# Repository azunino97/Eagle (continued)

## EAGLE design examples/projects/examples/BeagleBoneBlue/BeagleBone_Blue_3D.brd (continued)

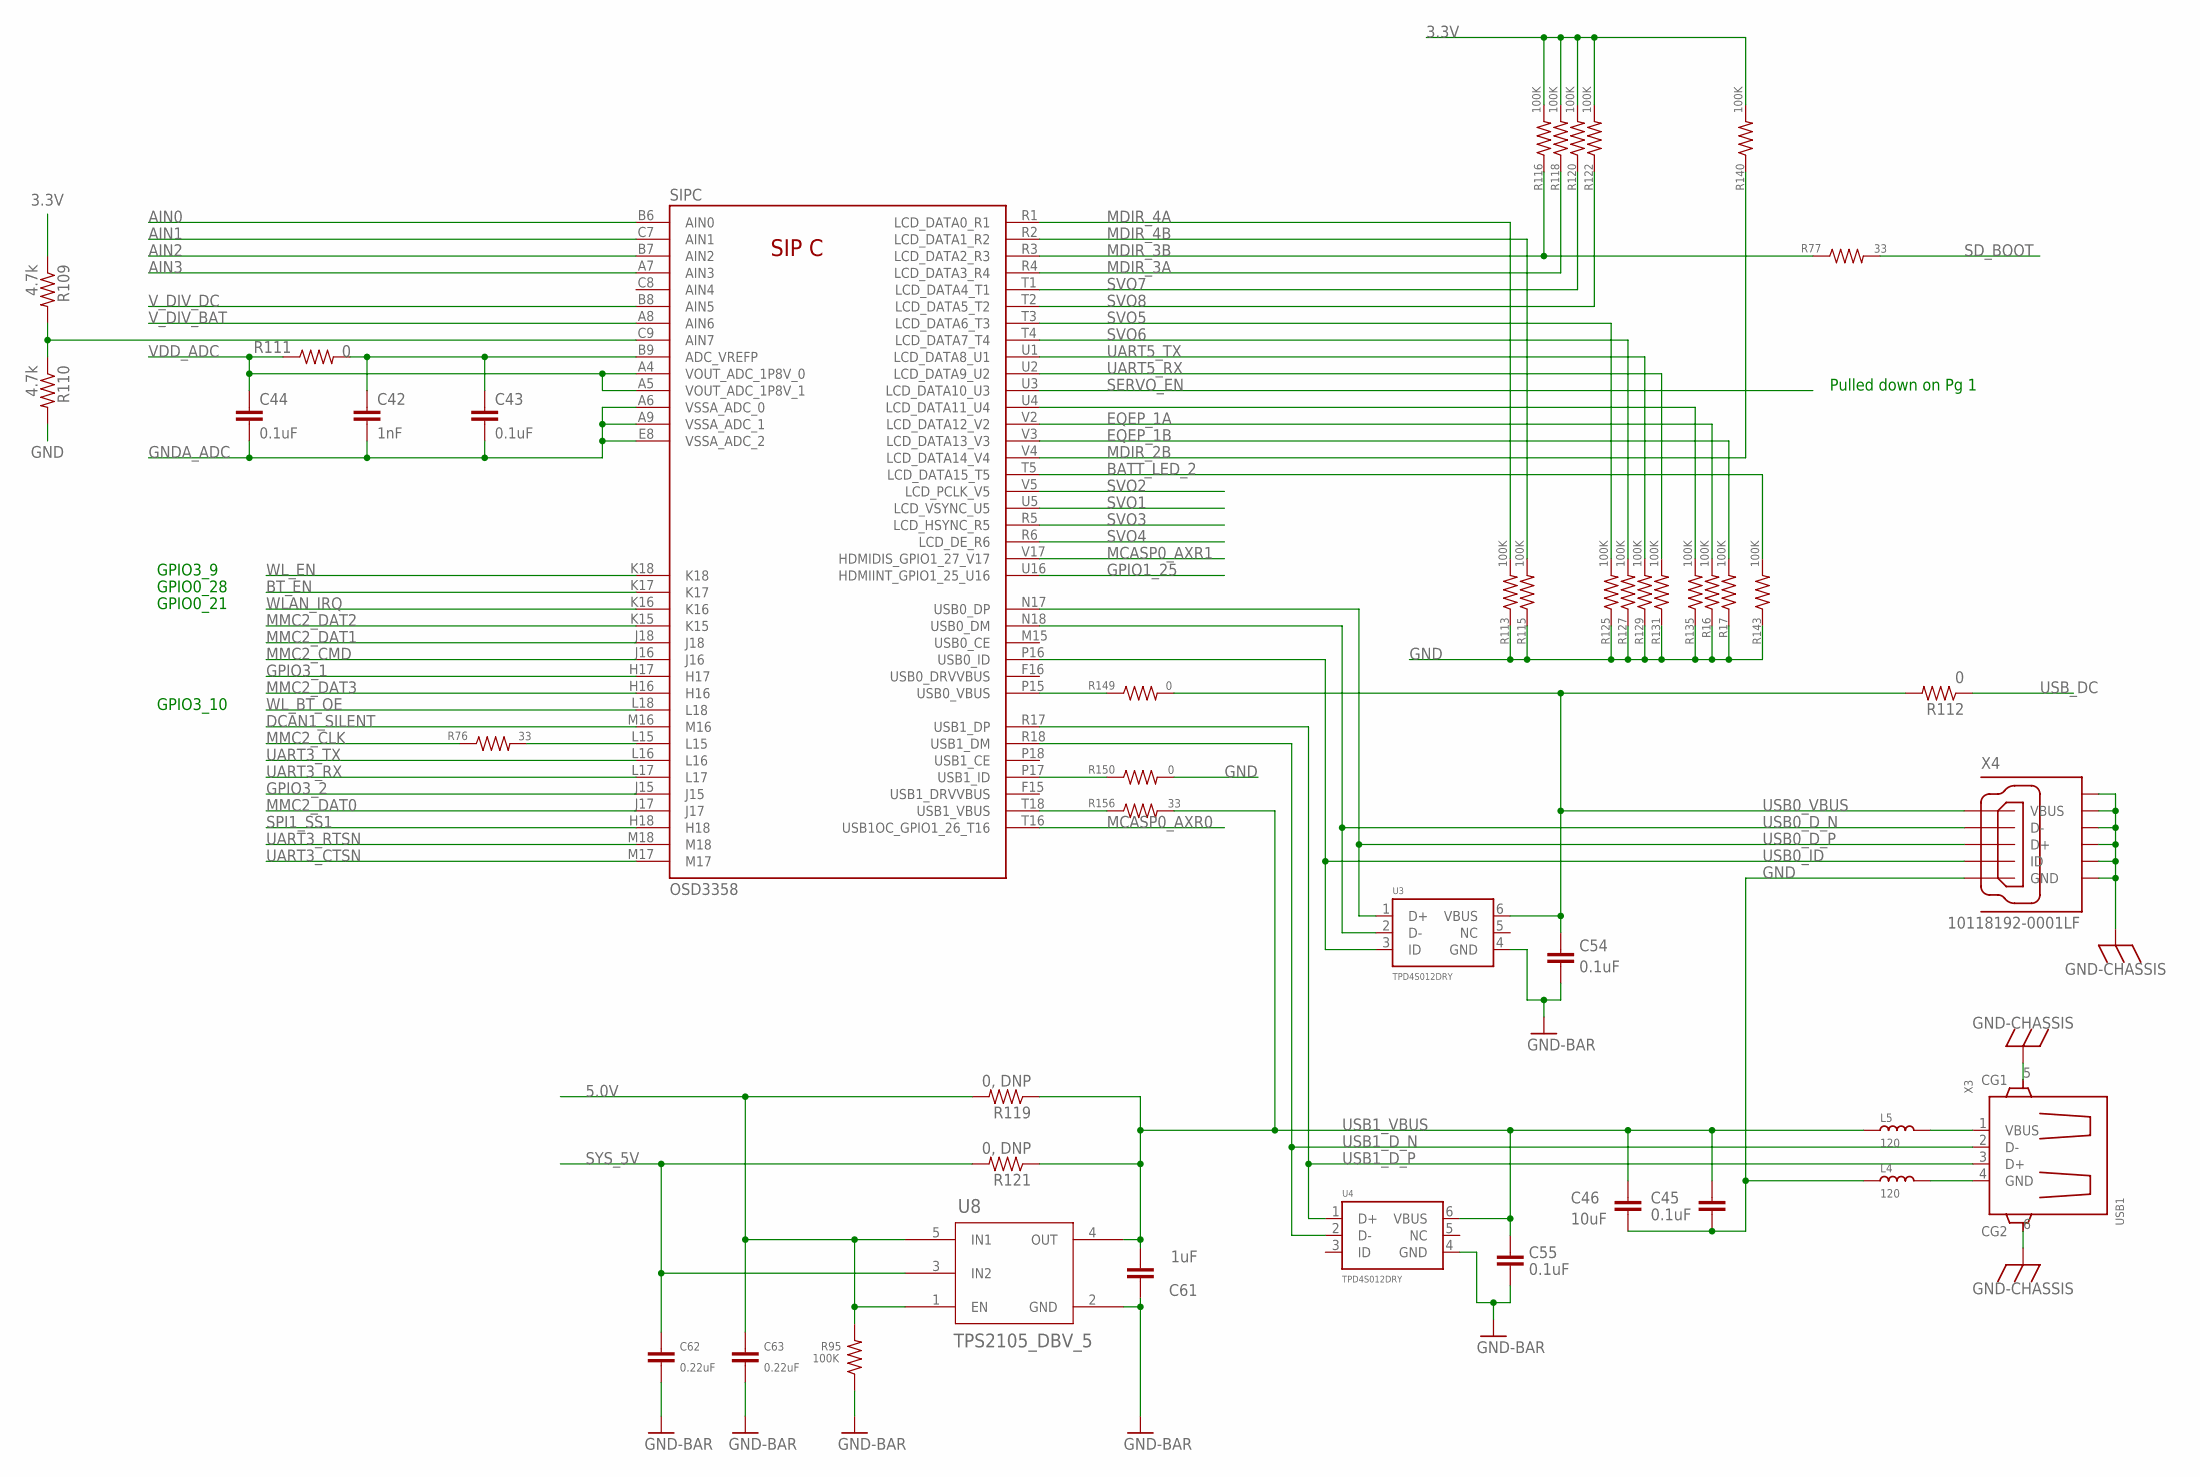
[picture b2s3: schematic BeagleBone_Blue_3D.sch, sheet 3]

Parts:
C42: 1nF; 0402-CAP
C43, C44, C45, C54, C55: 0.1uF; 0402-CAP
C46: 10uF; 0805
C61: 1uF; 0402-CAP
C62, C63: 0.22uF; 0402-CAP
L4, L5: 120; INDUCTOR_L0603
R16, R17, R95, R113, R115, R116, R118, R120, R122, R125, R127, R129, R131, R135, R140, R143: 100K; 0402-RES
R76, R77, R156: 33; 0402-RES
R109, R110: 4.7k; 0402-RES
R111, R149, R150: 0; 0402-RES
R112: 0; R0603
R119, R121: 0, DNP; R0603
SIP: OSD3358
U3, U4: TPD4S012DRY; SON-6(TI)-DRY
U8: TPS2105_DBV_5; DIODE_DBV5
X3: USB1; GHI2_USB_HOST_HORIZONTAL_W/CHASSIS_GND
X4: 10118192-0001LF; GHI-CONNECTORS_10118192-0001LF(MICRO-USB-B-AMPHENOL-FCI)

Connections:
3.3V: R109.1, R116.2, R118.2, R120.2, R122.2, R140.2; also elsewhere on the board
5.0V: C63.1, R95.2, R119.2, U8.1 (EN), U8.5 (IN1); also elsewhere on the board
AIN0: SIP.B6 (AIN0); also elsewhere on the board
AIN1: SIP.C7 (AIN1); also elsewhere on the board
AIN2: SIP.B7 (AIN2); also elsewhere on the board
AIN3: SIP.A7 (AIN3); also elsewhere on the board
BATT_LED_2: R143.2, SIP.T5 (LCD_DATA15_T5); also elsewhere on the board
BT_EN: SIP.K17; also elsewhere on the board
CGND: X3.5 (CG1), X3.6 (CG2), X4.CGND1 (SGND1), X4.CGND2 (SGND2), X4.CGND3 (SGND3), X4.CGND4 (SGND4), X4.CGND5 (SGND5), X4.CGND6 (SGND6); also elsewhere on the board
DCAN1_SILENT: SIP.M16; also elsewhere on the board
EQEP_1A: R16.2, SIP.V2 (LCD_DATA12_V2); also elsewhere on the board
EQEP_1B: R17.2, SIP.V3 (LCD_DATA13_V3); also elsewhere on the board
GND: C45.2, C46.2, C54.2, C55.2, C61.1, C62.2, C63.2, L4.1, R16.1, R17.1, R95.1, R110.2, R113.1, R115.1, R125.1, R127.1, R129.1, R131.1, R135.1, R143.1, R150.2, U3.4 (GND), U4.4 (GND), U8.2 (GND), X4.GND; also elsewhere on the board
GNDA_ADC: C42.2, C43.2, C44.2, SIP.A6 (VSSA_ADC_0), SIP.A9 (VSSA_ADC_1), SIP.E8 (VSSA_ADC_2)
GPIO1_25: SIP.U16 (HDMIINT_GPIO1_25_U16); also elsewhere on the board
GPIO3_1: SIP.H17; also elsewhere on the board
GPIO3_2: SIP.J15; also elsewhere on the board
MCASP0_AXR0: SIP.T16 (USB1OC_GPIO1_26_T16); also elsewhere on the board
MCASP0_AXR1: SIP.V17 (HDMIDIS_GPIO1_27_V17); also elsewhere on the board
MDIR_2B: R140.1, SIP.V4 (LCD_DATA14_V4); also elsewhere on the board
MDIR_3A: R118.1, SIP.R4 (LCD_DATA3_R4); also elsewhere on the board
MDIR_3B: R77.1, R116.1, SIP.R3 (LCD_DATA2_R3); also elsewhere on the board
MDIR_4A: R113.2, SIP.R1 (LCD_DATA0_R1); also elsewhere on the board
MDIR_4B: R115.2, SIP.R2 (LCD_DATA1_R2); also elsewhere on the board
MMC2_CLK: R76.1; also elsewhere on the board
MMC2_CMD: SIP.J16; also elsewhere on the board
MMC2_DAT0: SIP.J17; also elsewhere on the board
MMC2_DAT1: SIP.J18; also elsewhere on the board
MMC2_DAT2: SIP.K15; also elsewhere on the board
MMC2_DAT3: SIP.H16; also elsewhere on the board
unnamed: R76.2, SIP.L15
unnamed: R135.2, SIP.U4 (LCD_DATA11_U4)
unnamed: C42.1, C43.1, R111.2, SIP.B9 (ADC_VREFP)
unnamed: R109.2, R110.1, SIP.C9 (AIN7)
unnamed: R149.1, SIP.P15 (USB0_VBUS)
unnamed: R150.1, SIP.P17 (USB1_ID)
unnamed: L4.2, X3.4 (GND)
unnamed: R156.1, SIP.T18 (USB1_VBUS)
unnamed: L5.2, X3.1 (VBUS)
SD_BOOT: R77.2; also elsewhere on the board
SERVO_EN: SIP.U3 (LCD_DATA10_U3); also elsewhere on the board
SPI1_SS1: SIP.H18; also elsewhere on the board
SVO1: SIP.U5 (LCD_VSYNC_U5); also elsewhere on the board
SVO2: SIP.V5 (LCD_PCLK_V5); also elsewhere on the board
SVO3: SIP.R5 (LCD_HSYNC_R5); also elsewhere on the board
SVO4: SIP.R6 (LCD_DE_R6); also elsewhere on the board
SVO5: R125.2, SIP.T3 (LCD_DATA6_T3); also elsewhere on the board
SVO6: R127.2, SIP.T4 (LCD_DATA7_T4); also elsewhere on the board
SVO7: R120.1, SIP.T1 (LCD_DATA4_T1); also elsewhere on the board
SVO8: R122.1, SIP.T2 (LCD_DATA5_T2); also elsewhere on the board
SYS_5V: C62.1, R121.2, U8.3 (IN2); also elsewhere on the board
UART3_CTSN: SIP.M17; also elsewhere on the board
UART3_RTSN: SIP.M18; also elsewhere on the board
UART3_RX: SIP.L17; also elsewhere on the board
UART3_TX: SIP.L16; also elsewhere on the board
UART5_RX: R131.2, SIP.U2 (LCD_DATA9_U2); also elsewhere on the board
UART5_TX: R129.2, SIP.U1 (LCD_DATA8_U1); also elsewhere on the board
USB0_D_N: SIP.N18 (USB0_DM), U3.2 (D-), X4.D-
USB0_D_P: SIP.N17 (USB0_DP), U3.1 (D+), X4.D+
USB0_ID: SIP.P16 (USB0_ID), U3.3 (ID), X4.ID
USB0_VBUS: C54.1, R112.2, R149.2, U3.6 (VBUS), X4.VBUS
USB1_D_N: SIP.R18 (USB1_DM), U4.2 (D-), X3.2 (D-)
USB1_D_P: SIP.R17 (USB1_DP), U4.1 (D+), X3.3 (D+)
USB1_VBUS: C45.1, C46.1, C55.1, C61.2, L5.1, R119.1, R121.1, R156.2, U4.6 (VBUS), U8.4 (OUT)
USB_DC: R112.1; also elsewhere on the board
VDD_ADC: C44.1, R111.1, SIP.A4 (VOUT_ADC_1P8V_0), SIP.A5 (VOUT_ADC_1P8V_1); also elsewhere on the board
VIN_BAT_0: SIP.Y2 (VIN_BAT_0)
VIN_BAT_1: SIP.Y3 (VIN_BAT_1)
V_DIV_BAT: SIP.A8 (AIN6); also elsewhere on the board
V_DIV_DC: SIP.B8 (AIN5); also elsewhere on the board
WLAN_IRQ: SIP.K16; also elsewhere on the board
WL_BT_OE: SIP.L18; also elsewhere on the board
WL_EN: SIP.K18; also elsewhere on the board

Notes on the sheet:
Pulled down on Pg 1
GPIO3_9
GPIO0_28
GPIO0_21
GPIO3_10

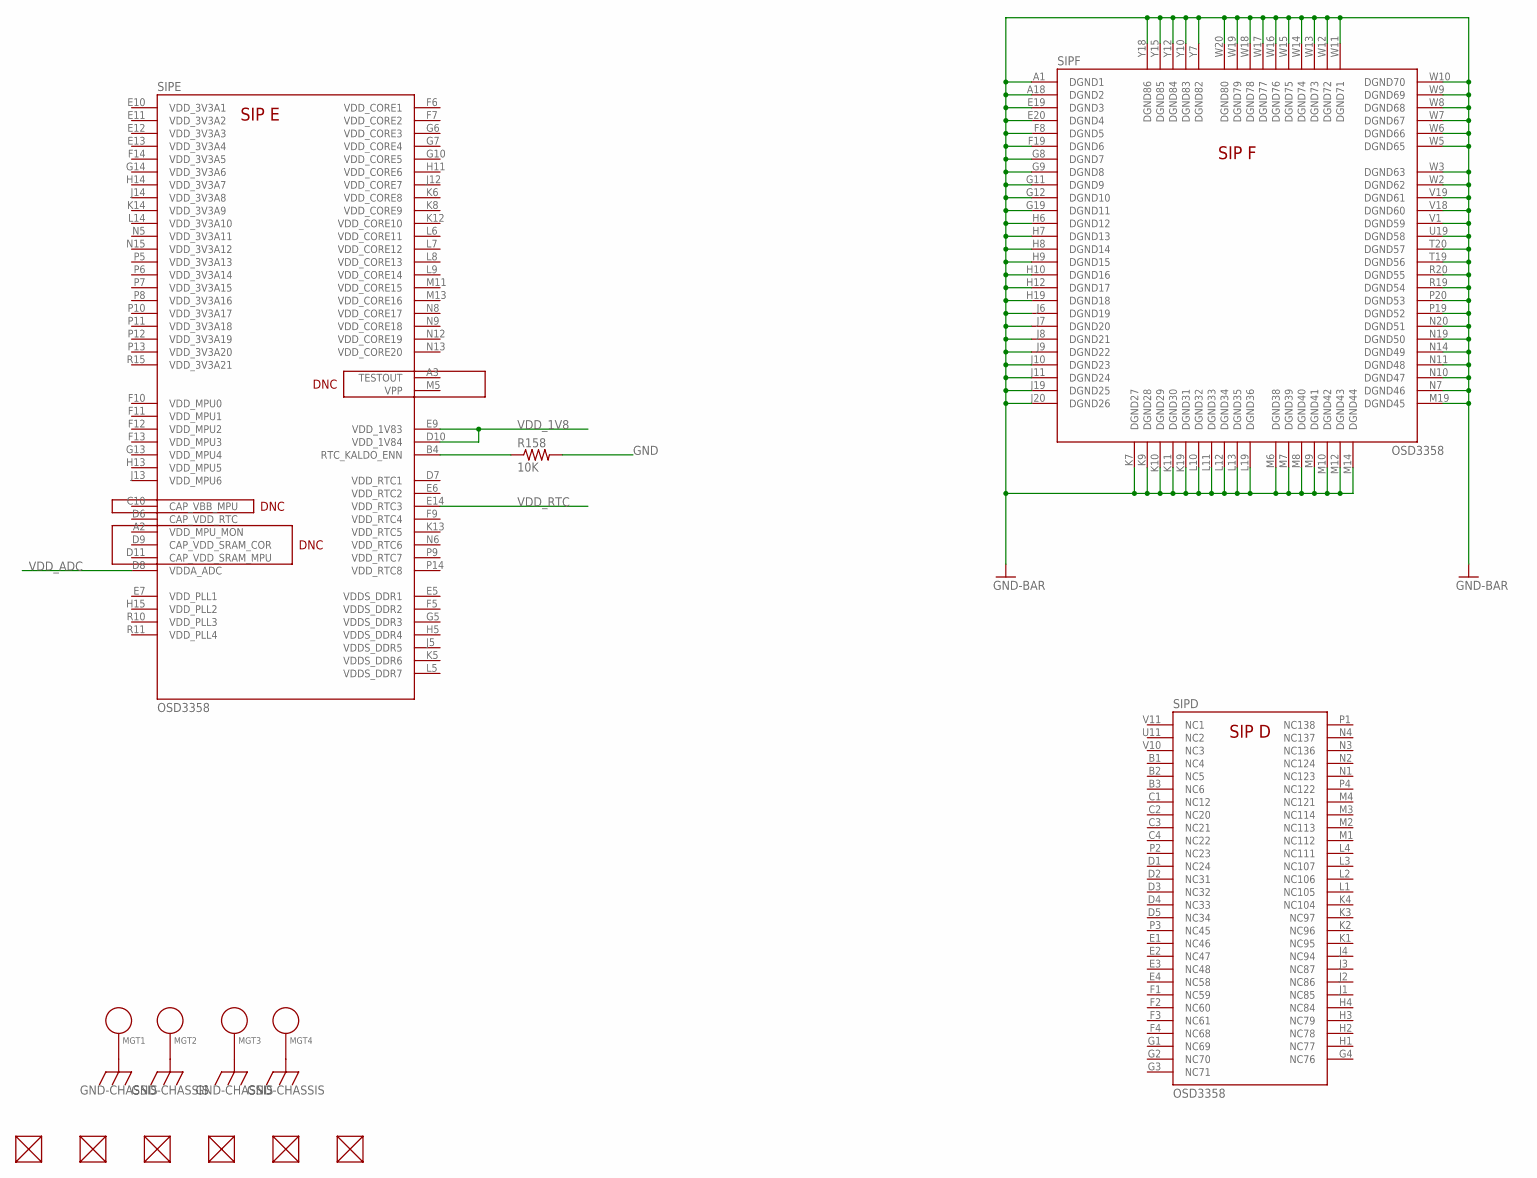
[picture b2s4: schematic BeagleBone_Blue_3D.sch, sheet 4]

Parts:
FUD1, FUD2, FUD3, FUD4, FUD5, FUD6: FIDUCIAL; GHI_FIDUCIAL_40MIL
MGT1, MGT2, MGT3, MGT4: MOUNTING_HOLE; BEAGLEBONEBLACK_MOUNTING_HOLE
R158: 10K; 0402-RES
SIP: OSD3358

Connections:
CGND: MGT1.P$1, MGT2.P$1, MGT3.P$1, MGT4.P$1; also elsewhere on the board
GND: R158.2, SIP.A1 (DGND1), SIP.A18 (DGND2), SIP.E19 (DGND3), SIP.E20 (DGND4), SIP.F8 (DGND5), SIP.F19 (DGND6), SIP.G8 (DGND7), SIP.G9 (DGND8), SIP.G11 (DGND9), SIP.G12 (DGND10), SIP.G19 (DGND11), SIP.H6 (DGND12), SIP.H7 (DGND13), SIP.H8 (DGND14), SIP.H9 (DGND15), SIP.H10 (DGND16), SIP.H12 (DGND17), SIP.H19 (DGND18), SIP.J6 (DGND19), SIP.J7 (DGND20), SIP.J8 (DGND21), SIP.J9 (DGND22), SIP.J10 (DGND23), SIP.J11 (DGND24), SIP.J19 (DGND25), SIP.J20 (DGND26), SIP.K7 (DGND27), SIP.K9 (DGND28), SIP.K10 (DGND29), SIP.K11 (DGND30), SIP.K19 (DGND31), SIP.L10 (DGND32), SIP.L11 (DGND33), SIP.L12 (DGND34), SIP.L13 (DGND35), SIP.L19 (DGND36), SIP.M6 (DGND38), SIP.M7 (DGND39), SIP.M8 (DGND40), SIP.M9 (DGND41), SIP.M10 (DGND42), SIP.M12 (DGND43), SIP.M14 (DGND44), SIP.M19 (DGND45), SIP.N7 (DGND46), SIP.N10 (DGND47), SIP.N11 (DGND48), SIP.N14 (DGND49), SIP.N19 (DGND50), SIP.N20 (DGND51), SIP.P19 (DGND52), SIP.P20 (DGND53), SIP.R19 (DGND54), SIP.R20 (DGND55), SIP.T19 (DGND56), SIP.T20 (DGND57), SIP.U19 (DGND58), SIP.V1 (DGND59), SIP.V18 (DGND60), SIP.V19 (DGND61), SIP.W2 (DGND62), SIP.W3 (DGND63), SIP.W5 (DGND65), SIP.W6 (DGND66), SIP.W7 (DGND67), SIP.W8 (DGND68), SIP.W9 (DGND69), SIP.W10 (DGND70), SIP.W11 (DGND71), SIP.W12 (DGND72), SIP.W13 (DGND73), SIP.W14 (DGND74), SIP.W15 (DGND75), SIP.W16 (DGND76), SIP.W17 (DGND77), SIP.W18 (DGND78), SIP.W19 (DGND79), SIP.W20 (DGND80), SIP.Y7 (DGND82), SIP.Y10 (DGND83), SIP.Y12 (DGND84), SIP.Y15 (DGND85), SIP.Y18 (DGND86); also elsewhere on the board
unnamed: R158.1, SIP.B4 (RTC_KALDO_ENN)
VDD_1V8: SIP.D10 (VDD_1V84), SIP.E9 (VDD_1V83); also elsewhere on the board
VDD_ADC: SIP.D8 (VDDA_ADC); also elsewhere on the board
VDD_RTC: SIP.E14 (VDD_RTC3); also elsewhere on the board
VIN_BAT_0: SIP.Y2 (VIN_BAT_0)
VIN_BAT_1: SIP.Y3 (VIN_BAT_1)

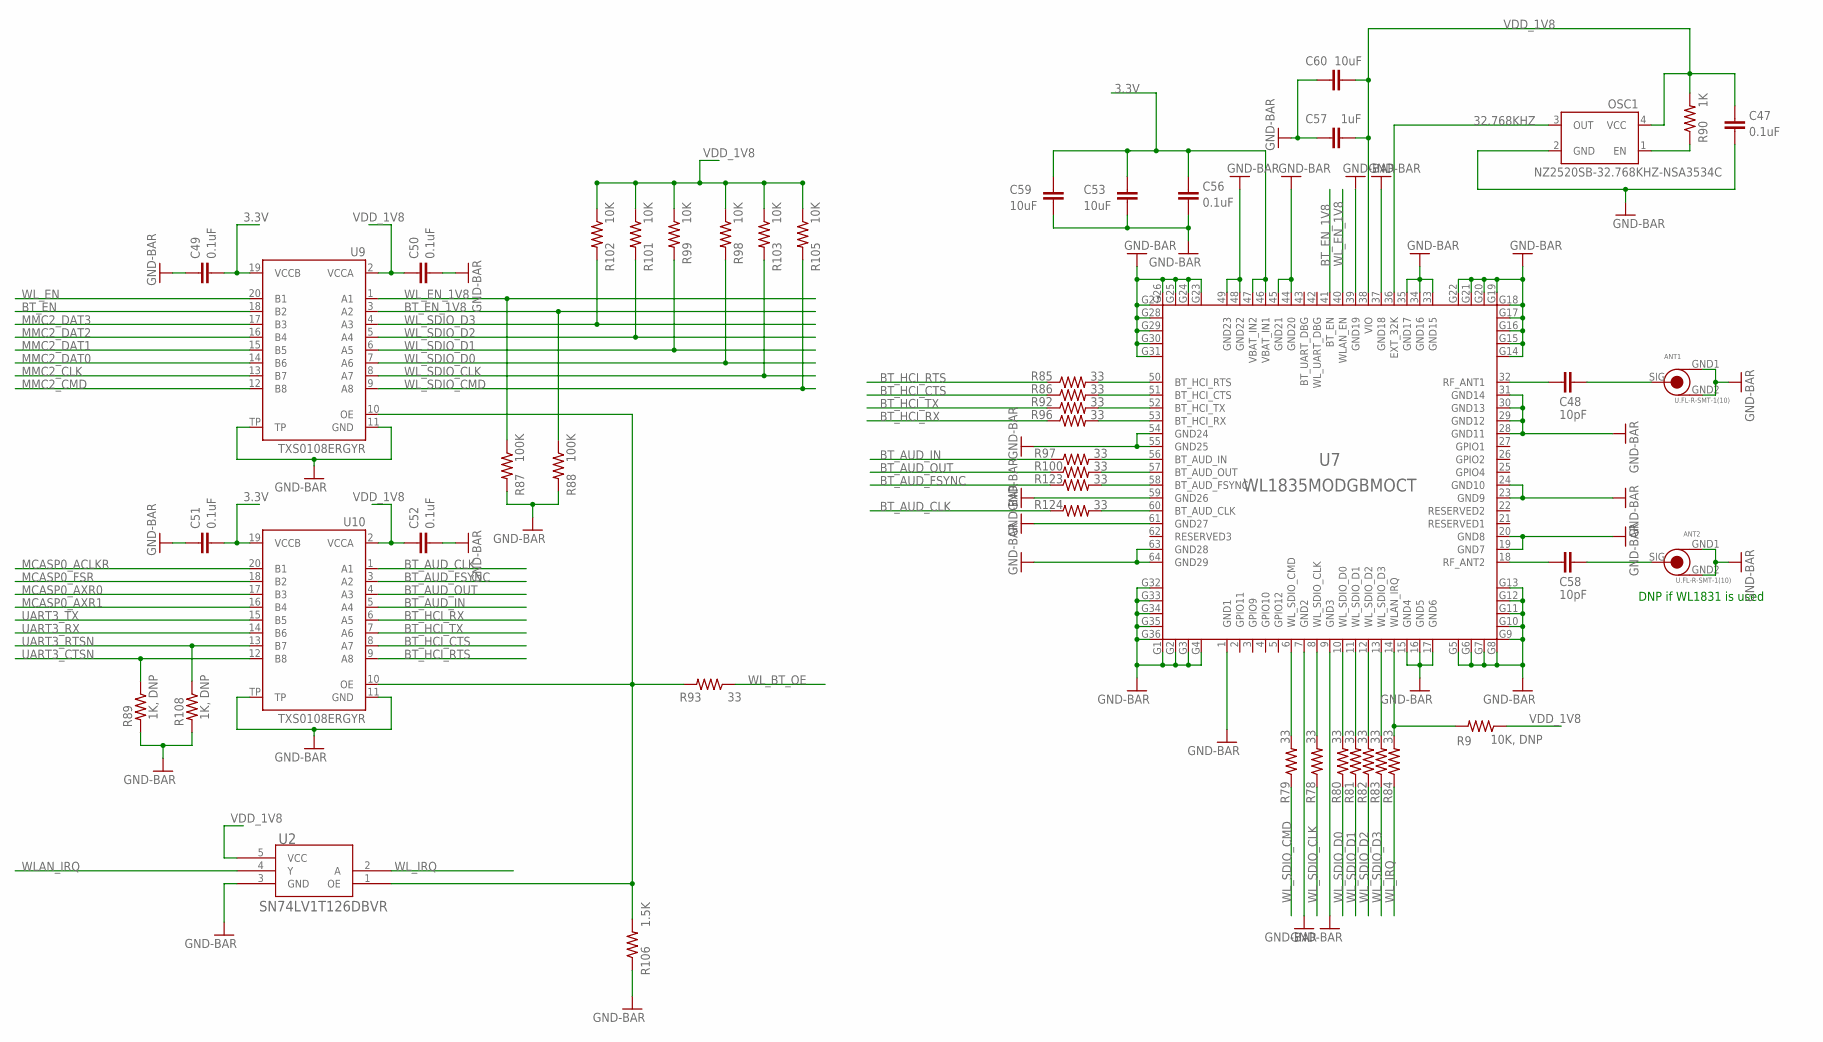
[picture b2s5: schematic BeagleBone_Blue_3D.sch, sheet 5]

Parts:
ANT1, ANT2: U.FL-R-SMT-1(10); GHI-CONNECTORS_U.FL-R-SMT-1
C47, C49, C50, C51, C52, C56: 0.1uF; 0402-CAP
C48, C58: 10pF; 0402-CAP
C53, C59, C60: 10uF; 0805
C57: 1uF; 0402-CAP
OSC1: NZ2520SB-32.768KHZ-NSA3534C; NZ2520S
R9: 10K, DNP; 0402-RES
R78, R79, R80, R81, R82, R83, R84, R85, R86, R92, R93, R96, R97, R100, R123, R124: 33; 0402-RES
R87, R88: 100K; 0402-RES
R89, R108: 1K, DNP; 0402-RES
R90: 1K; 0402-RES
R98, R99, R101, R102, R103, R105: 10K; 0402-RES
R106: 1.5K; 0402-RES
U2: SN74LV1T126DBVR; SOT95P280X145-5
U7: WL1835MODGBMOCT; MOC-100(TI)
U9, U10: TXS0108ERGYR; R-PVQFN-N20(TI)

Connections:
3.3V: C49.2, C51.2, C53.1, C56.1, C59.1, U7.46 (VBAT_IN1), U7.47 (VBAT_IN2), U9.19 (VCCB), U10.19 (VCCB); also elsewhere on the board
32.768KHZ: OSC1.3 (OUT), U7.36 (EXT_32K)
ALT.BUFF.OE: R93.2, R106.2, U2.1 (OE), U9.10 (OE), U10.10 (OE)
ANT1_A: C48.2, U7.32 (RF_ANT1)
ANT1_B: ANT1.SIG, C48.1
ANT2_A: C58.2, U7.18 (RF_ANT2)
ANT2_B: ANT2.SIG, C58.1
BT_AUD_CLK: R124.1, U10.1 (A1)
BT_AUD_FSYNC: R123.1, U10.3 (A2)
BT_AUD_IN: R97.1, U10.5 (A4)
BT_AUD_OUT: R100.1, U10.4 (A3)
BT_EN: U9.18 (B2); also elsewhere on the board
BT_EN_1V8: R88.1, U7.41 (BT_EN), U9.3 (A2)
BT_HCI_CTS: R86.1, U10.8 (A7)
BT_HCI_RTS: R85.1, U10.9 (A8)
BT_HCI_RX: R96.1, U10.6 (A5)
BT_HCI_TX: R92.1, U10.7 (A6)
GND: ANT1.GND1, ANT1.GND2, ANT2.GND1, ANT2.GND2, C47.2, C49.1, C50.2, C51.1, C52.2, C53.2, C56.2, C57.1, C59.2, C60.1, OSC1.2 (GND), R87.2, R88.2, R89.2, R106.1, R108.2, U2.3 (GND), U7.1 (GND1), U7.7 (GND2), U7.9 (GND3), U7.15 (GND4), U7.16 (GND5), U7.17 (GND6), U7.19 (GND7), U7.20 (GND8), U7.23 (GND9), U7.24 (GND10), U7.28 (GND11), U7.29 (GND12), U7.30 (GND13), U7.31 (GND14), U7.33 (GND15), U7.34 (GND16), U7.35 (GND17), U7.37 (GND18), U7.39 (GND19), U7.44 (GND20), U7.45 (GND21), U7.48 (GND22), U7.49 (GND23), U7.54 (GND24), U7.55 (GND25), U7.59 (GND26), U7.61 (GND27), U7.63 (GND28), U7.64 (GND29), U7.G1, U7.G2, U7.G3, U7.G4, U7.G5, U7.G6, U7.G7, U7.G8, U7.G9, U7.G10, U7.G11, U7.G12, U7.G13, U7.G14, U7.G15, U7.G16, U7.G17, U7.G18, U7.G19, U7.G20, U7.G21, U7.G22, U7.G23, U7.G24, U7.G25, U7.G26, U7.G27, U7.G28, U7.G29, U7.G30, U7.G31, U7.G32, U7.G33, U7.G34, U7.G35, U7.G36, U9.11 (GND), U9.TP, U10.11 (GND), U10.TP; also elsewhere on the board
MCASP0_ACLKR: U10.20 (B1); also elsewhere on the board
MCASP0_AXR0: U10.17 (B3); also elsewhere on the board
MCASP0_AXR1: U10.16 (B4); also elsewhere on the board
MCASP0_FSR: U10.18 (B2); also elsewhere on the board
MMC2_CLK: U9.13 (B7); also elsewhere on the board
MMC2_CMD: U9.12 (B8); also elsewhere on the board
MMC2_DAT0: U9.14 (B6); also elsewhere on the board
MMC2_DAT1: U9.15 (B5); also elsewhere on the board
MMC2_DAT2: U9.16 (B4); also elsewhere on the board
MMC2_DAT3: U9.17 (B3); also elsewhere on the board
unnamed: OSC1.1 (EN), R90.1
unnamed: R100.2, U7.57 (BT_AUD_OUT)
unnamed: R9.2, R84.2, U7.14 (WLAN_IRQ)
unnamed: R83.2, U7.13 (WL_SDIO_D3)
unnamed: R82.2, U7.12 (WL_SDIO_D2)
unnamed: R81.2, U7.11 (WL_SDIO_D1)
unnamed: R80.2, U7.10 (WL_SDIO_D0)
unnamed: R78.2, U7.8 (WL_SDIO_CLK)
unnamed: R79.2, U7.6 (WL_SDIO_CMD)
unnamed: R85.2, U7.50 (BT_HCI_RTS)
unnamed: R86.2, U7.51 (BT_HCI_CTS)
unnamed: R92.2, U7.52 (BT_HCI_TX)
unnamed: R96.2, U7.53 (BT_HCI_RX)
unnamed: R97.2, U7.56 (BT_AUD_IN)
unnamed: R123.2, U7.58 (BT_AUD_FSYNC)
unnamed: R124.2, U7.60 (BT_AUD_CLK)
UART3_CTSN: R89.1, U10.12 (B8); also elsewhere on the board
UART3_RTSN: R108.1, U10.13 (B7); also elsewhere on the board
UART3_RX: U10.14 (B6); also elsewhere on the board
UART3_TX: U10.15 (B5); also elsewhere on the board
VDD_1V8: C47.1, C50.1, C52.1, C57.2, C60.2, OSC1.4 (VCC), R9.1, R90.2, R98.1, R99.1, R101.1, R102.1, R103.1, R105.1, U2.5 (VCC), U7.38 (VIO), U9.2 (VCCA), U10.2 (VCCA); also elsewhere on the board
WLAN_IRQ: U2.4 (Y); also elsewhere on the board
WL_BT_OE: R93.1; also elsewhere on the board
WL_EN: U9.20 (B1); also elsewhere on the board
WL_EN_1V8: R87.1, U7.40 (WLAN_EN), U9.1 (A1)
WL_IRQ: R84.1, U2.2 (A)
WL_SDIO_CLK: R78.1, R103.2, U9.8 (A7)
WL_SDIO_CMD: R79.1, R105.2, U9.9 (A8)
WL_SDIO_D0: R80.1, R98.2, U9.7 (A6)
WL_SDIO_D1: R81.1, R99.2, U9.6 (A5)
WL_SDIO_D2: R82.1, R101.2, U9.5 (A4)
WL_SDIO_D3: R83.1, R102.2, U9.4 (A3)

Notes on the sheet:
DNP if WL1831 is used

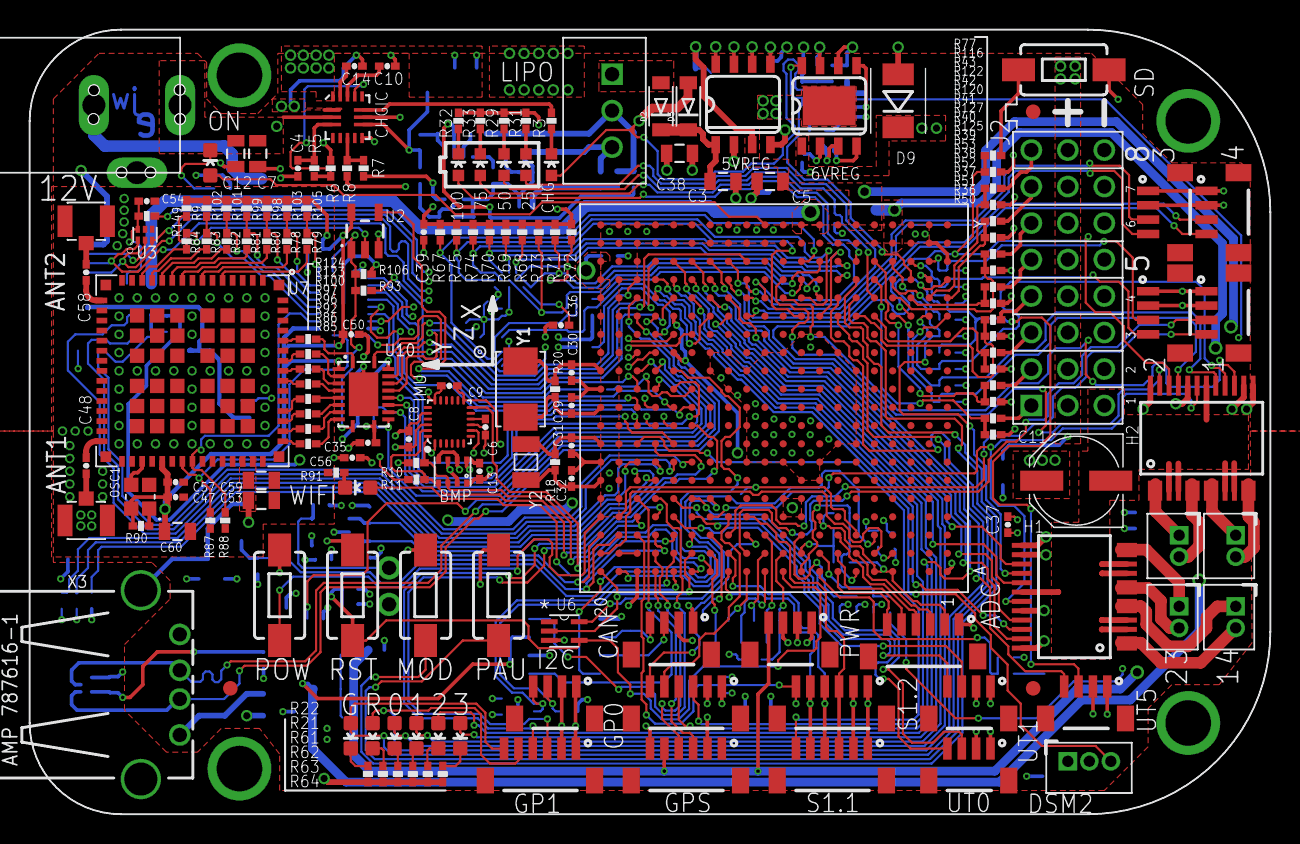
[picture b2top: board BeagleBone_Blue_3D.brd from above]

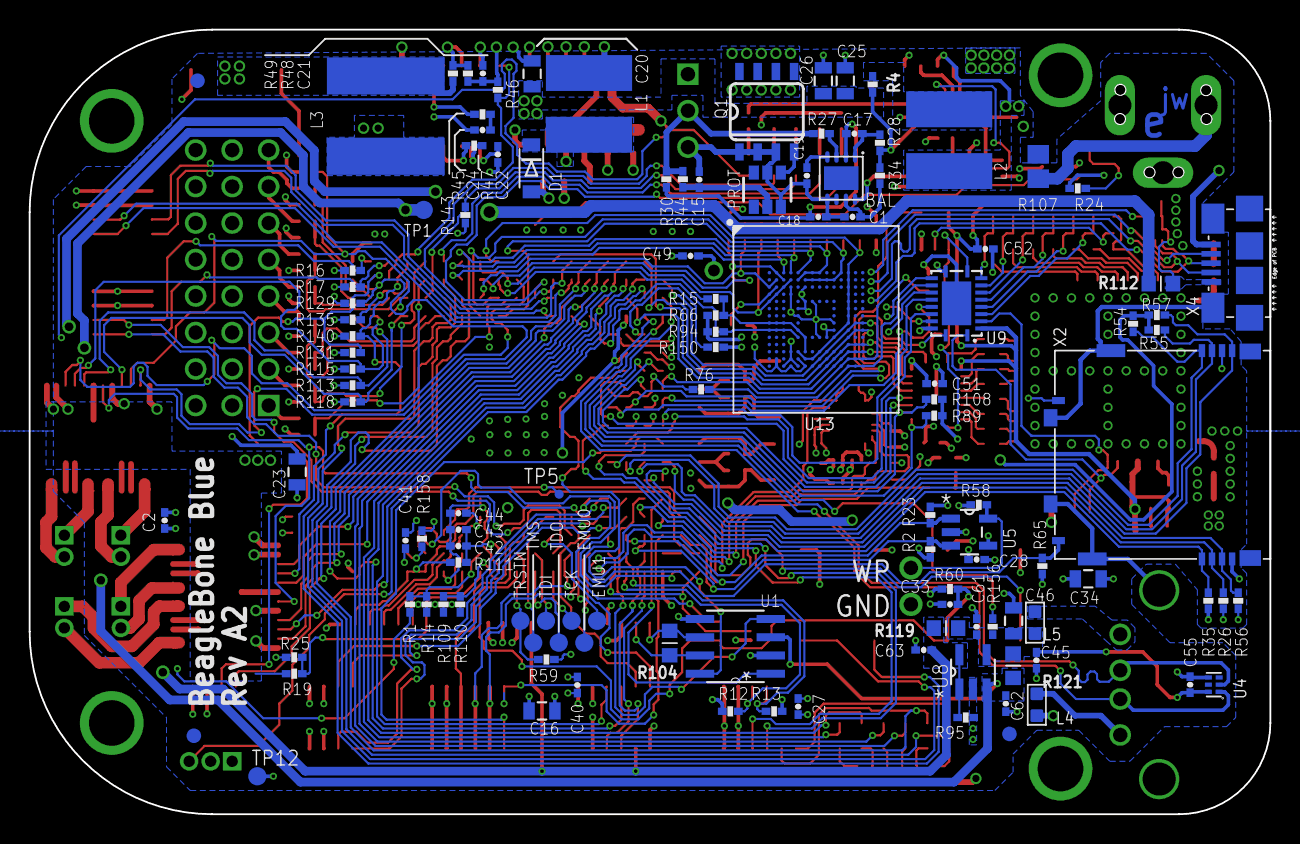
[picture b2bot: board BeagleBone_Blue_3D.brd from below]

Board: 4 copper layers, 86.4 x 54.6 mm, 302 parts (122 on the bottom side), 268 nets.

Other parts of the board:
BOARD: BEAGLEBONE_BLUE_NO_HOLES
U$1: BATTERY_INDICATOR_LEFT
U$2: XYZ_BIG

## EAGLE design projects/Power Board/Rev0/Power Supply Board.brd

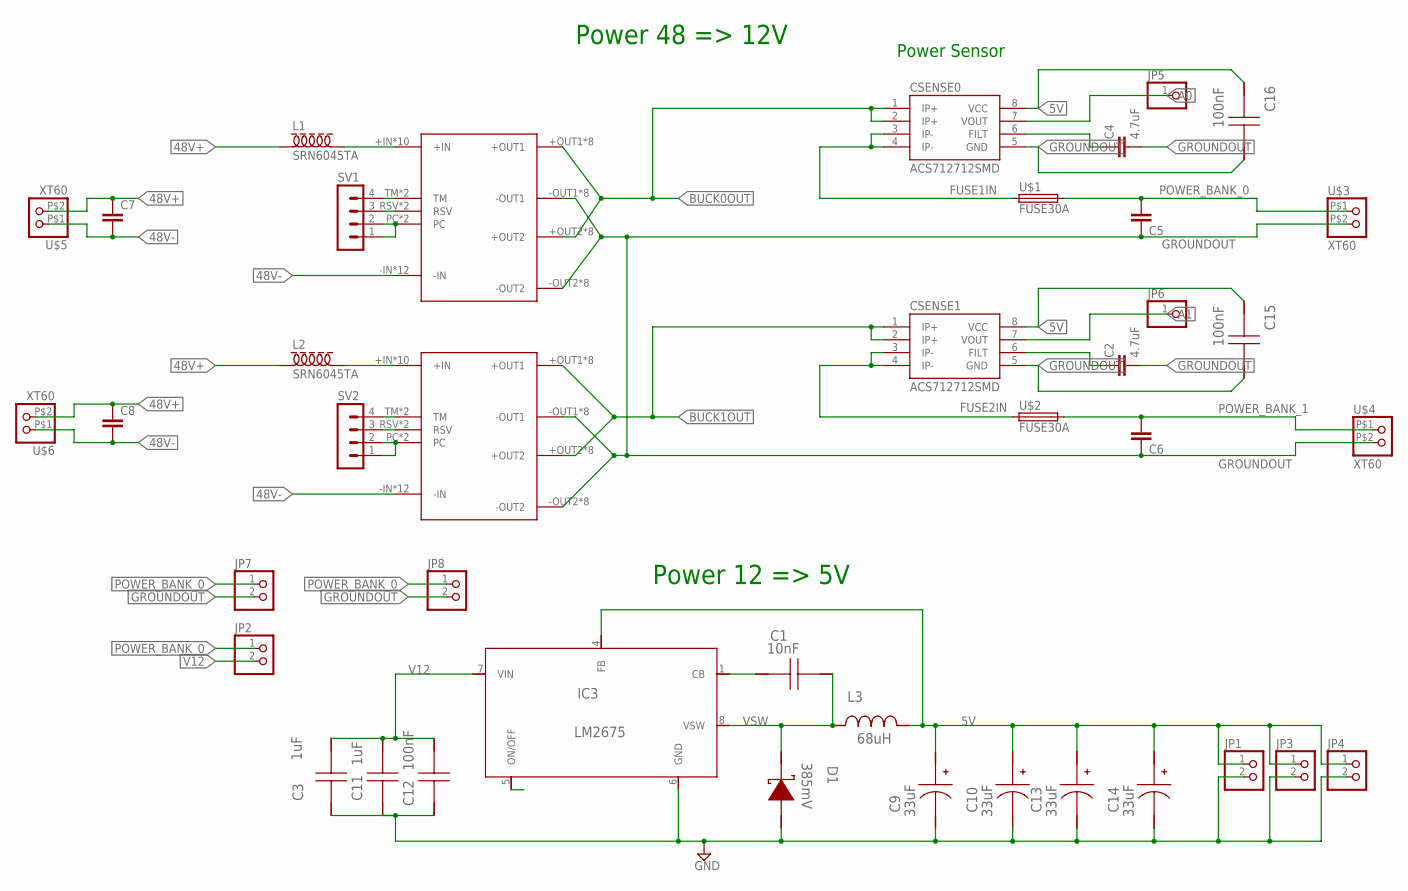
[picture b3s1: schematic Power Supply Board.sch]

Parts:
C1: 10nF; 0805
C2, C4: 4.7uF; 0603-CAP
C3, C11: 1uF; 0603
C5, C6, C7, C8: C2,5-3; C2.5-3
C9, C10, C13, C14: 33uF; CAPSMT_6_A09
C12, C15, C16: 100nF; 0805
CSENSE0, CSENSE1: ACS712712SMD; SO08
D1: 385mV; SOD-123
IC3: LM2675; M08A
JP1, JP2, JP3, JP4, JP7, JP8: PINHD-1X2; 1X02
JP5, JP6: PINHD-1X1; 1X01
L1, L2: SRN6045TA
L3: 68uH; SRU1028
SV1, SV2: MA04-1
U$1, U$2: FUSE30A
U$3, U$4, U$5, U$6: XT60
VC1, VC2: VOLTAGECONVERTER

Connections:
5V: C9.1 (+), C10.1 (+), C13.1 (+), C14.1 (+), C15.1, C16.1, CSENSE0.8 (VCC), CSENSE1.8 (VCC), IC3.4 (FB), JP1.1, JP3.1, JP4.1, L3.2
48V+: C7.1, C8.1, L1.P$1 (1), L2.P$1 (1), U$5.P$2 (2), U$6.P$2 (2)
48V-: C7.2, C8.2, U$5.P$1 (1), U$6.P$1 (1), VC1.-IN, VC1.-IN@0 (-IN), VC1.-IN@1 (-IN), VC1.-IN@2 (-IN), VC1.-IN@3 (-IN), VC1.-IN@4 (-IN), VC1.-IN@5 (-IN), VC1.-IN@6 (-IN), VC1.-IN@7 (-IN), VC1.-IN@8 (-IN), VC1.-IN@9 (-IN), VC1.-IN@10 (-IN), VC2.-IN, VC2.-IN@0 (-IN), VC2.-IN@1 (-IN), VC2.-IN@2 (-IN), VC2.-IN@3 (-IN), VC2.-IN@4 (-IN), VC2.-IN@5 (-IN), VC2.-IN@6 (-IN), VC2.-IN@7 (-IN), VC2.-IN@8 (-IN), VC2.-IN@9 (-IN), VC2.-IN@10 (-IN)
48VIN1: L1.P$2 (2), VC1.+IN, VC1.+IN@1 (+IN), VC1.+IN@2 (+IN), VC1.+IN@3 (+IN), VC1.+IN@4 (+IN), VC1.+IN@5 (+IN), VC1.+IN@6 (+IN), VC1.+IN@7 (+IN), VC1.+IN@8 (+IN), VC1.+IN@9 (+IN)
48VIN2: L2.P$2 (2), VC2.+IN, VC2.+IN@1 (+IN), VC2.+IN@2 (+IN), VC2.+IN@3 (+IN), VC2.+IN@4 (+IN), VC2.+IN@5 (+IN), VC2.+IN@6 (+IN), VC2.+IN@7 (+IN), VC2.+IN@8 (+IN), VC2.+IN@9 (+IN)
A0: CSENSE0.7 (VOUT), JP5.1
A1: CSENSE1.7 (VOUT), JP6.1
BUCK0OUT: CSENSE0.1 (IP+), CSENSE0.2 (IP+), VC1.+OUT1, VC1.+OUT1@1 (+OUT1), VC1.+OUT1@2 (+OUT1), VC1.+OUT1@3 (+OUT1), VC1.+OUT1@4 (+OUT1), VC1.+OUT1@5 (+OUT1), VC1.+OUT1@6 (+OUT1), VC1.+OUT1@7 (+OUT1), VC1.+OUT2, VC1.+OUT2@1 (+OUT2), VC1.+OUT2@2 (+OUT2), VC1.+OUT2@3 (+OUT2), VC1.+OUT2@4 (+OUT2), VC1.+OUT2@5 (+OUT2), VC1.+OUT2@6 (+OUT2), VC1.+OUT2@7 (+OUT2)
BUCK1OUT: CSENSE1.1 (IP+), CSENSE1.2 (IP+), VC2.+OUT1, VC2.+OUT1@1 (+OUT1), VC2.+OUT1@2 (+OUT1), VC2.+OUT1@3 (+OUT1), VC2.+OUT1@4 (+OUT1), VC2.+OUT1@5 (+OUT1), VC2.+OUT1@6 (+OUT1), VC2.+OUT1@7 (+OUT1), VC2.+OUT2, VC2.+OUT2@1 (+OUT2), VC2.+OUT2@2 (+OUT2), VC2.+OUT2@3 (+OUT2), VC2.+OUT2@4 (+OUT2), VC2.+OUT2@5 (+OUT2), VC2.+OUT2@6 (+OUT2), VC2.+OUT2@7 (+OUT2)
CB: C1.2, IC3.1 (CB)
FILT1: C4.1, CSENSE0.6 (FILT)
FILT2: C2.1, CSENSE1.6 (FILT)
FUSE1IN: CSENSE0.3 (IP-), CSENSE0.4 (IP-), U$1.P$1 (1), U$1.P$2 (1)
FUSE2IN: CSENSE1.3 (IP-), CSENSE1.4 (IP-), U$2.P$1 (1), U$2.P$2 (1)
GROUNDOUT: C2.2, C3.2, C4.2, C5.1, C6.1, C9.2 (-), C10.2 (-), C11.2, C12.2, C13.2 (-), C14.2 (-), C15.2, C16.2, CSENSE0.5 (GND), CSENSE1.5 (GND), D1.2 (A), IC3.6 (GND), JP1.2, JP3.2, JP4.2, JP7.2, JP8.2, U$3.P$2 (2), U$4.P$2 (2), VC1.-OUT1, VC1.-OUT1@1 (-OUT1), VC1.-OUT1@2 (-OUT1), VC1.-OUT1@3 (-OUT1), VC1.-OUT1@4 (-OUT1), VC1.-OUT1@5 (-OUT1), VC1.-OUT1@6 (-OUT1), VC1.-OUT1@7 (-OUT1), VC1.-OUT2, VC1.-OUT2@1 (-OUT2), VC1.-OUT2@2 (-OUT2), VC1.-OUT2@3 (-OUT2), VC1.-OUT2@4 (-OUT2), VC1.-OUT2@5 (-OUT2), VC1.-OUT2@6 (-OUT2), VC1.-OUT2@7 (-OUT2), VC2.-OUT1, VC2.-OUT1@1 (-OUT1), VC2.-OUT1@2 (-OUT1), VC2.-OUT1@3 (-OUT1), VC2.-OUT1@4 (-OUT1), VC2.-OUT1@5 (-OUT1), VC2.-OUT1@6 (-OUT1), VC2.-OUT1@7 (-OUT1), VC2.-OUT2, VC2.-OUT2@1 (-OUT2), VC2.-OUT2@2 (-OUT2), VC2.-OUT2@3 (-OUT2), VC2.-OUT2@4 (-OUT2), VC2.-OUT2@5 (-OUT2), VC2.-OUT2@6 (-OUT2), VC2.-OUT2@7 (-OUT2)
unnamed: SV1.3, VC1.RSV, VC1.RSV@1 (RSV)
unnamed: SV2.3, VC2.RSV, VC2.RSV@1 (RSV)
PC1: SV1.1, SV1.2, SV2.1, SV2.2, VC1.PC, VC1.PC21 (PC), VC2.PC, VC2.PC21 (PC)
POWER_BANK_0: C5.2, JP2.1, JP7.1, JP8.1, U$1.P$3 (2), U$1.P$4 (2), U$3.P$1 (1)
POWER_BANK_1: C6.2, U$2.P$3 (2), U$2.P$4 (2), U$4.P$1 (1)
TM1: SV1.4, VC1.TM, VC1.TM@1 (TM)
TM2: SV2.4, VC2.TM, VC2.TM@1 (TM)
V12: C3.1, C11.1, C12.1, IC3.7 (VIN), JP2.2
VSW: C1.1, D1.1 (K), IC3.8 (VSW), L3.1

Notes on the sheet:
Power 12 => 5V
Power 48 => 12V
Power Sensor

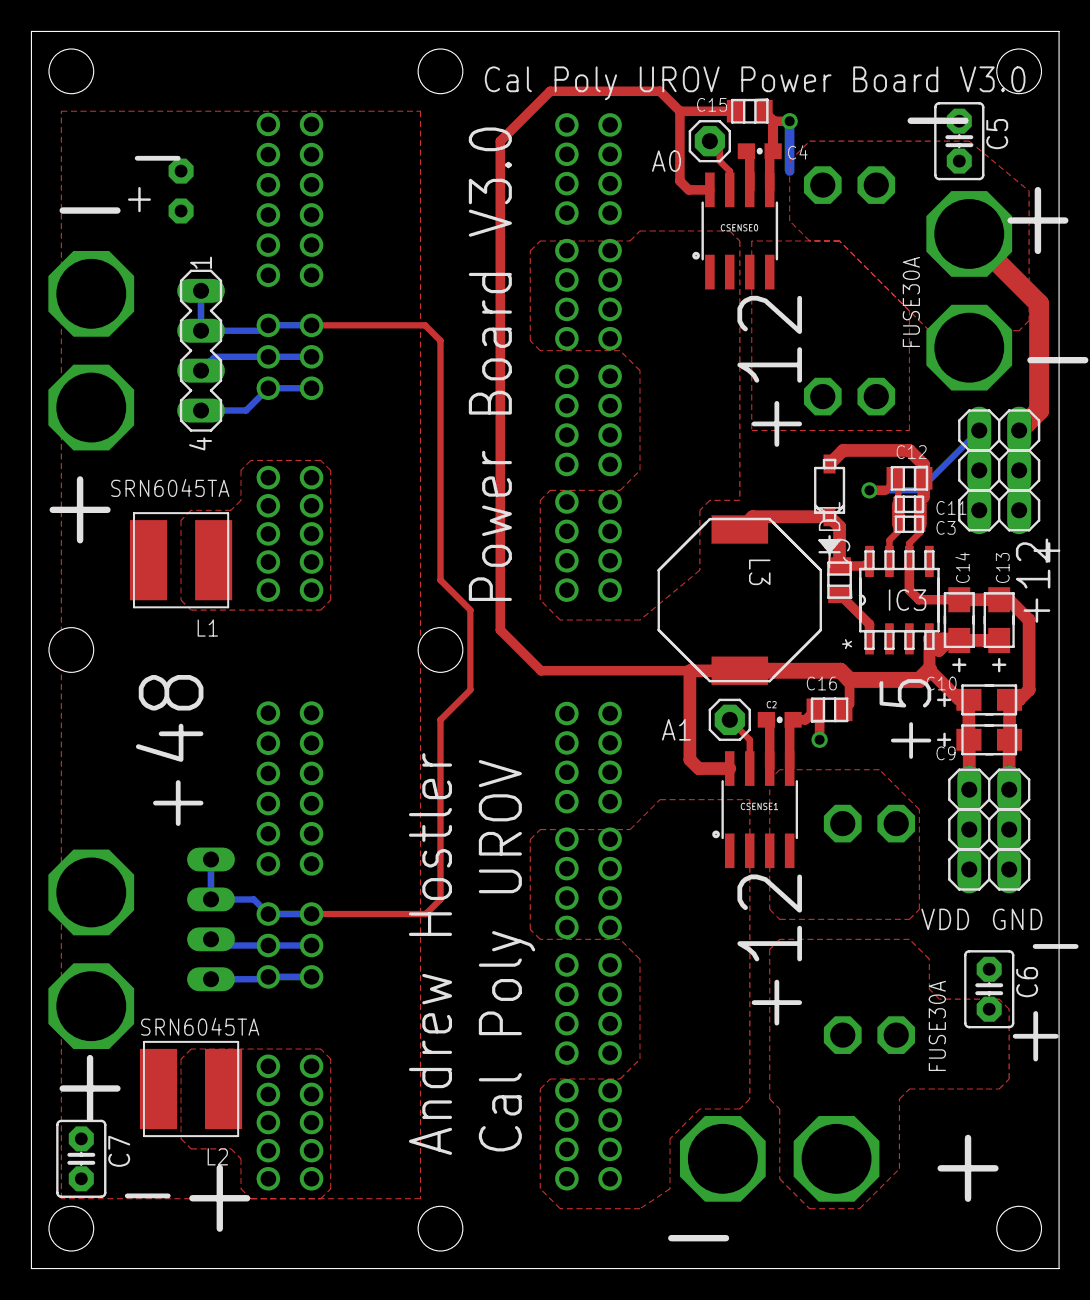
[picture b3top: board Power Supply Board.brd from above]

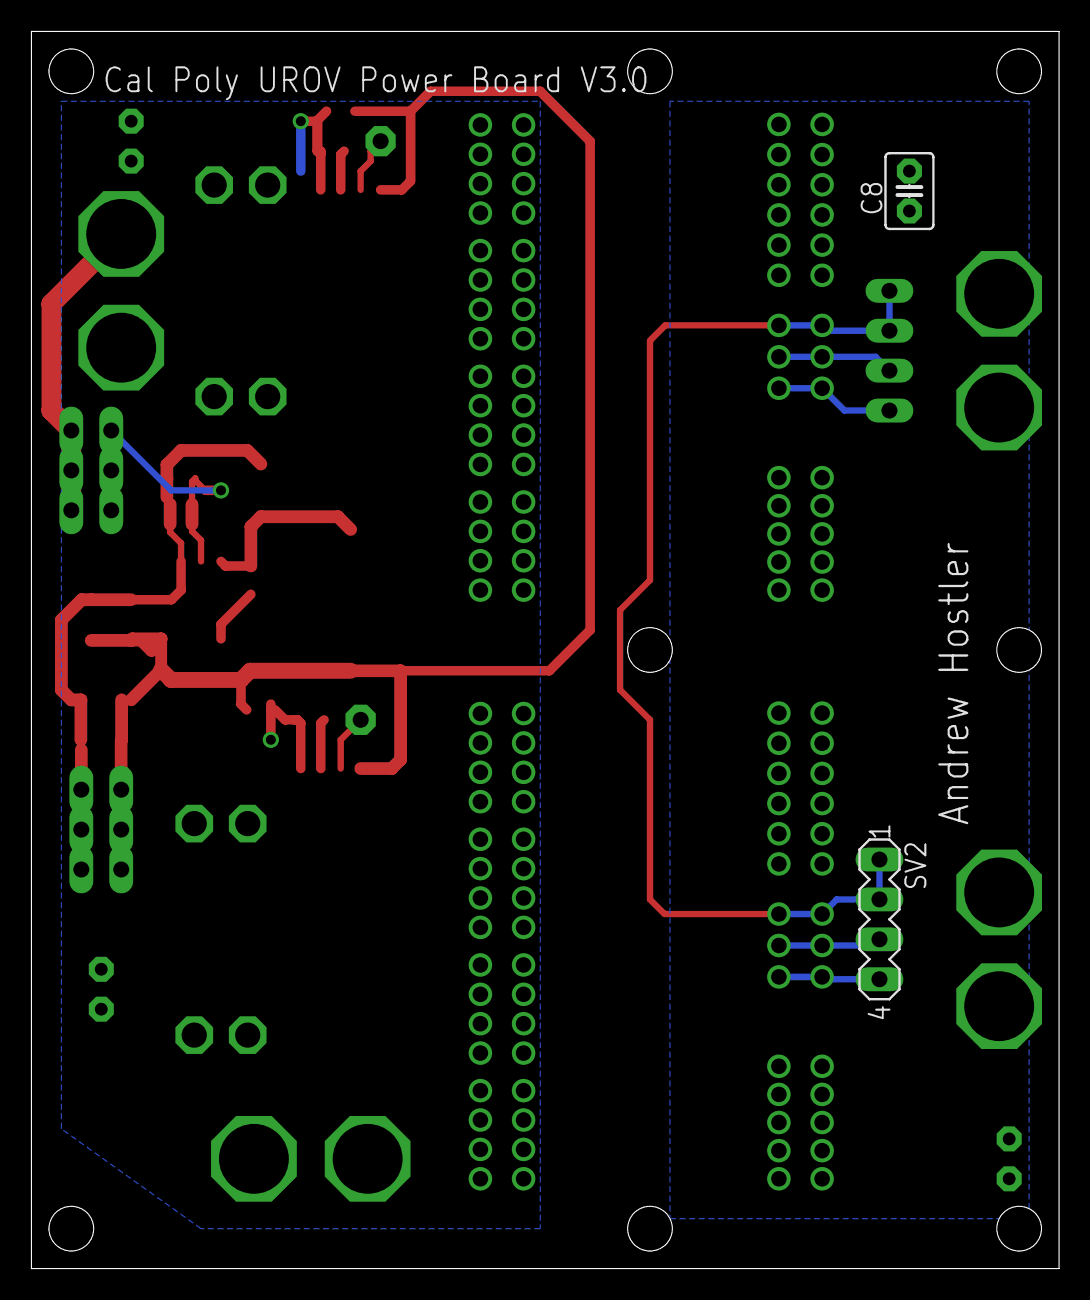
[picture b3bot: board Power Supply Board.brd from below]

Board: 2 copper layers, 65.4 x 78.7 mm, 41 parts (5 on the bottom side), 24 nets.
